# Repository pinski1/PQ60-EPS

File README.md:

#PQ60-EPS
An Electronic Power System in the PocketQube 60 form factor

**Untested**

The PQ60 Electrical Power System board is a system board for pico-satellites that connects to the solar arrays, charges the internal battery and provides protected battery voltage and protected +3V3 regulated supplies.

Uses @Pinski1's [PQ60-Template](https://github.com/pinski1/PQ60-Template) as the starting point for the design.

##Features
* Integrated active solar array maximum power point tracking.
* Battery charge management for Lithium Ion and Lithium Polymer batteries.
* Battery under-voltage protection.
* 3.3V and Raw Battery buses with over-current, over-voltage and reverse voltage protection.
* Monitoring of voltage, current and power of the solar cells, battery voltage and +3V3 via I<sup>2</sup>C interface.
* Kill switch connector to disable the satellite while in deployment tube.
* Compatible with the updated [PQ60 standard](http://pq60.info/).

##To Do
- [ ] Order PCBs
- [ ] Generate, format and order parts list
- [ ] Write firmware for KL05

##System

<!-- Block diagram -->

###Top
Telemetry of the EPS is provided on I<sup>2</sup>C by the Freescale [KL05](http://www.freescale.com/webapp/sps/site/prod_summary.jsp?code=KL0) ARM Cortex-M0 micro-controller which monitors the voltage, current and power at two points:

* The output of the raw battery 
* The output of the +3.3 Volt regulator

This will give real-time figures for the power flowing into the battery as well as the power being consumed by system loads. It also monitors the status pins and makes them available.

To protect this mission critical board against faults on other boards both the raw battery and regulated outputs have protection components to guard against over voltage, reverse voltage and over current. This is provided by Texas Instruments chip [TPS2553](http://www.ti.com/product/tps2553).

To ensure that the satellite logic is powered up successfully a Microchip [MCP130T](http://www.microchip.com/wwwproducts/Devices.aspx?product=MCP130) reset supervisor will hold the reset pin low until the the +3.3 Volt regulated supply is stable when it will release the reset pin.

###MPPT
To ensure that the maximum energy is harvested from the solar cells they are connected to a Maximum Power Point Tracker (MPPT). This reduces the current draw so as to efficiently transfer the harvested energy to the battery. This function is provided by a LinearTech [LTC3105](http://www.linear.com/product/LTC3105).

###IDIODE
To combine the 2 MPPT outputs a set of ideal diodes are used. These combine total energy harvested from the solar arrays and provide it to the Battery Management System (BMS). This function is provided by a LinearTech [LTC4413](http://www.linear.com/product/LTC4413).

###BMS
To store the energy from the solar arrays for future use it must be used to charge a battery. This stored energy can be used for the steady state operations of the satellite as well as peak operations such as transmitting or receiving data via the radio. This function is provided by a [MAX8606](http://www.maximintegrated.com/en/products/power/battery-management/MAX8606.html).

###SMPS
To provide a regulated +3.3 Volts a switched mode power supply is used. This converts the battery voltage to a stable +3.3 Volts and provides up to 750 milliamps of current to the rest of the subsystems. This function is provided by a [TPS63001](http://www.ti.com/product/tps63001).

##Connection Diagram

<!-- image -->

|Connector|     Type      |     Use        |
|---------|---------------|----------------|
|X2,3     | 4 way JST SHT | 2 Solar Arrays |
|X4       | 3 way JST SHT | Battery        |
|X5       | 2 way JST SHT | Kill Switch(s) |
|X1-Top   | 60 way FX6C   | PQ60 interface |
|X1-Bot   | 60 way FX6C   | PQ60 interface |

##Licensing
The hardware is released under [Creative Commons Attribution 3.0](https://creativecommons.org/licenses/by/3.0/).

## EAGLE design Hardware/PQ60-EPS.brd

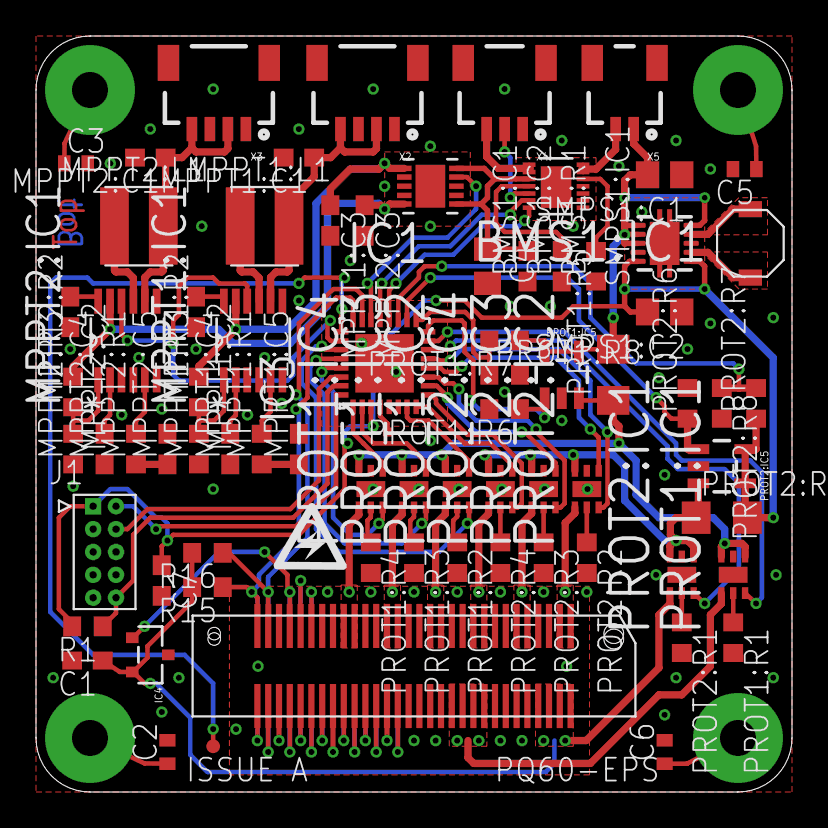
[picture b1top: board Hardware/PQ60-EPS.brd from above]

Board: 2 copper layers, 42.0 x 42.0 mm, 77 parts (1 on the bottom side), 95 nets.

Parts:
B1: PQ60-PINS; PQ60_PINS
BMS1:C1: 4.7uF; C0603
BMS1:C2: 100nF; C0603
BMS1:IC1: MAX8606; DFN300X300X80-15N
BMS1:R1: 2k; R0603
C1: 10nF; C0603
C2, C3, C5, C6: 100pF; C0402
C4: 4.7uF 10V; C0805
C7: 100nF; C0603
IC1: LTC4413; DFN300X300X80-11N
IC3: MKL05Z32VFM4; QFN50P500X500X100-33N
IC4: SOT23-R
J1: FTS-105-01-L-D; SAMTEC_FTS-105-01-L-D
MPPT1:C1, MPPT1:C3, MPPT2:C1, MPPT2:C3: 10uF; C0603
MPPT1:C2, MPPT2:C2: 1uF; C0603
MPPT1:C4, MPPT2:C4: 4.7uF; C0603
MPPT1:C5, MPPT2:C5: 10nF; C0603
MPPT1:IC1, MPPT2:IC1: LTC3105; SOP65P490X110-12N
MPPT1:L1, MPPT2:L1: 10uH; WE-TPC_3816
MPPT1:R1, MPPT2:R1: 75k; R0603
MPPT1:R2, MPPT2:R2: 1M33; R0603
MPPT1:R3, MPPT2:R3: 392k; R0603
PROT1:IC1, PROT1:IC2, PROT1:IC3, PROT1:IC4, PROT2:IC1, PROT2:IC2, PROT2:IC3, PROT2:IC4: TPS2553DRVT; SON65P200X200X80-7N
PROT1:IC5, PROT2:IC5: SOT23-5
PROT1:R1, PROT2:R1: 27k; R0603
PROT1:R2, PROT1:R3, PROT1:R4, PROT2:R2, PROT2:R3, PROT2:R4: 52k; R0603
PROT1:R5, PROT2:R5: 0R025; R1206
PROT1:R6, PROT2:R6: 10k 1%; R0603
PROT1:R7, PROT2:R7: 820k 1%; R0603
PROT1:R8, PROT2:R8: 200k 1%; R0603
R1: 10k; R0603
R15, R16: DNP; R0603
SMPS1:C1, SMPS1:C2: 10uF; C0805
SMPS1:IC1: TPS63001; DRC-S-PVSON-N10
SMPS1:L1: 2.2uH; VLF4012A
TP1: TEST-POINT2; PAD.02X.02
TP2: TEST-POINT3; PAD.03X.03
X1-BOT: FX8C-60S-SV
X1-TOP: FX8C-60P-SV
X2, X3: 1X04-1MM-RA
X4: 1X03-1MM-RA
X5: 1X02-1MM-RA

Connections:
!RST: IC4.1, X1-BOT.27, X1-TOP.27
+3V3_I_SEN: IC3.18, PROT2:IC5.1, PROT2:R6.1
+3V3_SW[0]_!FAULT!: IC3.14, PROT2:IC1.3
+3V3_SW[1]: PROT2:IC2.1, X1-BOT.1, X1-BOT.2, X1-TOP.1, X1-TOP.2
+3V3_SW[1]_!FAULT!: IC3.13, PROT2:IC2.3
+3V3_SW[1]_EN: IC3.12, PROT2:IC2.4
+3V3_SW[2]: PROT2:IC3.1, X1-BOT.5, X1-BOT.6, X1-TOP.5, X1-TOP.6
+3V3_SW[2]_!FAULT!: IC3.11, PROT2:IC3.3
+3V3_SW[2]_EN: IC3.10, PROT2:IC3.4
+3V3_SW[3]: PROT2:IC4.1, X1-BOT.9, X1-BOT.10, X1-TOP.9, X1-TOP.10
+3V3_SW[3]_!FAULT!: IC3.9, PROT2:IC4.3
+3V3_SW[3]_EN: IC3.8, PROT2:IC4.4
+3V3_UNPRO: C7.1, IC3.3, J1.1, PROT2:IC5.4, PROT2:IC5.5, PROT2:R5.2, PROT2:R7.1, R1.2, SMPS1:C2.2, SMPS1:IC1.1, SMPS1:IC1.10
+3V3_V_SEN: IC3.19, PROT2:R7.2, PROT2:R8.1
BMS1:BATT_PROG: BMS1:IC1.12, BMS1:R1.2
BMS1:VL: BMS1:C2.2, BMS1:IC1.4
BMS_!CHG!: BMS1:IC1.6, IC3.21
BMS_!PGD!: BMS1:IC1.7, IC3.20
GND: BMS1:C1.1, BMS1:C2.1, BMS1:IC1.8, BMS1:IC1.9, BMS1:IC1.10, BMS1:IC1.11, BMS1:IC1.15, BMS1:R1.1, C1.2, C2.2, C3.2, C4.2, C5.2, C6.2, C7.2, IC1.2, IC1.3, IC1.4, IC1.11, IC3.5, IC3.6, IC3.33, IC4.3, J1.3, J1.5, J1.7, J1.9, MPPT1:C1.2, MPPT1:C2.2, MPPT1:C3.2, MPPT1:C4.1, MPPT1:C5.2, MPPT1:IC1.3, MPPT1:IC1.6, MPPT1:IC1.7, MPPT1:R3.1, MPPT2:C1.2, MPPT2:C2.2, MPPT2:C3.2, MPPT2:C4.1, MPPT2:C5.2, MPPT2:IC1.3, MPPT2:IC1.6, MPPT2:IC1.7, MPPT2:R3.1, PROT1:IC1.5, PROT1:IC1.7, PROT1:IC2.5, PROT1:IC2.7, PROT1:IC3.5, PROT1:IC3.7, PROT1:IC4.5, PROT1:IC4.7, PROT1:IC5.2, PROT1:R1.2, PROT1:R2.2, PROT1:R3.2, PROT1:R4.2, PROT1:R6.2, PROT1:R8.2, PROT2:IC1.5, PROT2:IC1.7, PROT2:IC2.5, PROT2:IC2.7, PROT2:IC3.5, PROT2:IC3.7, PROT2:IC4.5, PROT2:IC4.7, PROT2:IC5.2, PROT2:R1.2, PROT2:R2.2, PROT2:R3.2, PROT2:R4.2, PROT2:R6.2, PROT2:R8.2, SMPS1:C1.1, SMPS1:C2.1, SMPS1:IC1.3, SMPS1:IC1.9, SMPS1:IC1.TH, SMPS1:IC1.TH@1, SMPS1:IC1.TH@2, X1-BOT.3, X1-BOT.4, X1-BOT.7, X1-BOT.8, X1-BOT.11, X1-BOT.12, X1-BOT.15, X1-BOT.16, X1-BOT.19, X1-BOT.20, X1-BOT.23, X1-BOT.24, X1-BOT.28, X1-BOT.45, X1-BOT.46, X1-BOT.47, X1-BOT.48, X1-BOT.53, X1-BOT.54, X1-BOT.55, X1-BOT.56, X1-TOP.3, X1-TOP.4, X1-TOP.7, X1-TOP.8, X1-TOP.11, X1-TOP.12, X1-TOP.15, X1-TOP.16, X1-TOP.19, X1-TOP.20, X1-TOP.23, X1-TOP.24, X1-TOP.28, X1-TOP.45, X1-TOP.46, X1-TOP.47, X1-TOP.48, X1-TOP.53, X1-TOP.54, X1-TOP.55, X1-TOP.56, X2.1, X2.3, X3.1, X3.3, X4.1
GPIO[0]: X1-BOT.25, X1-TOP.25
GPIO[1]: X1-BOT.26, X1-TOP.26
GPIO[2]: X1-BOT.34, X1-TOP.34
GPIO[3]: X1-BOT.35, X1-TOP.35
GPIO[4]: X1-BOT.36, X1-TOP.36
GPIO[5]: X1-BOT.37, X1-TOP.37
GPIO[6]: X1-BOT.38, X1-TOP.38
GPIO[7]: X1-BOT.39, X1-TOP.39
GPIO[8]: X1-BOT.40, X1-TOP.40
GPIO[9]: X1-BOT.41, X1-TOP.41
GPIO[10]: X1-BOT.42, X1-TOP.42
GPIO[11]: X1-BOT.43, X1-TOP.43
GPIO[12]: X1-BOT.44, X1-TOP.44
I2C_INT: IC3.25, TP2.P$1
I2C_SCL: IC3.23, R16.1, X1-BOT.29, X1-TOP.29
I2C_SDA: IC3.24, R15.1, X1-BOT.30, X1-TOP.30
IDIODE_STAT: IC1.9, IC3.22
MPPT1:AUX: MPPT1:C2.1, MPPT1:IC1.12
MPPT1:FB: MPPT1:IC1.1, MPPT1:R2.1, MPPT1:R3.2
MPPT1:LDO: MPPT1:C4.2, MPPT1:IC1.2
MPPT1:MPPC: MPPT1:IC1.5, MPPT1:R1.2
MPPT1:SW: MPPT1:IC1.9, MPPT1:L1.2
MPPT1:THM: MPPT1:C5.1, MPPT1:R1.1
MPPT2:AUX: MPPT2:C2.1, MPPT2:IC1.12
MPPT2:FB: MPPT2:IC1.1, MPPT2:R2.1, MPPT2:R3.2
MPPT2:LDO: MPPT2:C4.2, MPPT2:IC1.2
MPPT2:MPPC: MPPT2:IC1.5, MPPT2:R1.2
MPPT2:SW: MPPT2:IC1.9, MPPT2:L1.2
MPPT2:THM: MPPT2:C5.1, MPPT2:R1.1
MPPT_PGD: IC3.26, MPPT1:IC1.10, MPPT2:IC1.10
unnamed: B1.1, C2.1
unnamed: B1.2, C3.1
unnamed: B1.3, C5.1
unnamed: B1.4, C6.1
unnamed: IC3.4, TP1.P$1
PRO1: C1.1, IC4.2, PROT2:IC1.1, R15.2, R16.2, X1-BOT.57, X1-BOT.58, X1-BOT.59, X1-BOT.60, X1-TOP.57, X1-TOP.58, X1-TOP.59, X1-TOP.60
PROT1:IN_SEN: PROT1:IC1.4, PROT1:IC1.6, PROT1:IC2.6, PROT1:IC3.6, PROT1:IC4.6, PROT1:IC5.3, PROT1:R5.1
PROT1:I_LIM_SW1: PROT1:IC2.2, PROT1:R2.1
PROT1:I_LIM_SW2: PROT1:IC3.2, PROT1:R3.1
PROT1:I_LIM_SW3: PROT1:IC4.2, PROT1:R4.1
PROT1:I_LIM_VCC: PROT1:IC1.2, PROT1:R1.1
PROT2:IN_SEN: PROT2:IC1.4, PROT2:IC1.6, PROT2:IC2.6, PROT2:IC3.6, PROT2:IC4.6, PROT2:IC5.3, PROT2:R5.1
PROT2:I_LIM_SW1: PROT2:IC2.2, PROT2:R2.1
PROT2:I_LIM_SW2: PROT2:IC3.2, PROT2:R3.1
PROT2:I_LIM_SW3: PROT2:IC4.2, PROT2:R4.1
PROT2:I_LIM_VCC: PROT2:IC1.2, PROT2:R1.1
RESET: IC3.31, J1.10, R1.1
SMPS1:N$1: SMPS1:IC1.4, SMPS1:L1.P$1
SMPS1:N$2: SMPS1:IC1.2, SMPS1:L1.P$2
SOLAR[1..2]: MPPT1:C1.1, MPPT1:IC1.8, MPPT1:L1.1, X2.2, X2.4
SOLAR[3..4]: MPPT2:C1.1, MPPT2:IC1.8, MPPT2:L1.1, X3.2, X3.4
SPI_MISO: X1-BOT.32, X1-TOP.32
SPI_MOSI: X1-BOT.31, X1-TOP.31
SPI_SCK: X1-BOT.33, X1-TOP.33
SWD_CLK: IC3.30, J1.4
SWD_DIO: IC3.32, J1.2
S_ARRAY_1: IC1.1, MPPT1:C3.1, MPPT1:IC1.11, MPPT1:R2.2
S_ARRAY_2: IC1.5, MPPT2:C3.1, MPPT2:IC1.11, MPPT2:R2.2
THM: BMS1:IC1.5, X4.2
VBAT: PROT1:IC1.1, X1-BOT.49, X1-BOT.50, X1-BOT.51, X1-BOT.52, X1-TOP.49, X1-TOP.50, X1-TOP.51, X1-TOP.52
VBAT_I_SEN: IC3.16, PROT1:IC5.1, PROT1:R6.1
VBAT_SW[0]_!FAULT!: IC3.15, PROT1:IC1.3
VBAT_SW[1]: PROT1:IC2.1, X1-BOT.13, X1-BOT.14, X1-TOP.13, X1-TOP.14
VBAT_SW[1]_!FAULT!: IC3.27, PROT1:IC2.3
VBAT_SW[1]_EN: IC3.7, PROT1:IC2.4
VBAT_SW[2]: PROT1:IC3.1, X1-BOT.17, X1-BOT.18, X1-TOP.17, X1-TOP.18
VBAT_SW[2]_!FAULT!: IC3.28, PROT1:IC3.3
VBAT_SW[2]_EN: IC3.2, PROT1:IC3.4
VBAT_SW[3]: PROT1:IC4.1, X1-BOT.21, X1-BOT.22, X1-TOP.21, X1-TOP.22
VBAT_SW[3]_!FAULT!: IC3.29, PROT1:IC4.3
VBAT_SW[3]_EN: IC3.1, PROT1:IC4.4
VBAT_V_SEN: IC3.17, PROT1:R7.2, PROT1:R8.1
VSOL: BMS1:C1.2, BMS1:IC1.3, C4.1, IC1.6, IC1.10
VSYS: BMS1:IC1.13, BMS1:IC1.14, X5.2
VSYS_SW: PROT1:IC5.4, PROT1:IC5.5, PROT1:R5.2, PROT1:R7.1, SMPS1:C1.2, SMPS1:IC1.5, SMPS1:IC1.6, SMPS1:IC1.7, SMPS1:IC1.8, X5.1
V_BAT: BMS1:IC1.1, BMS1:IC1.2, X4.3

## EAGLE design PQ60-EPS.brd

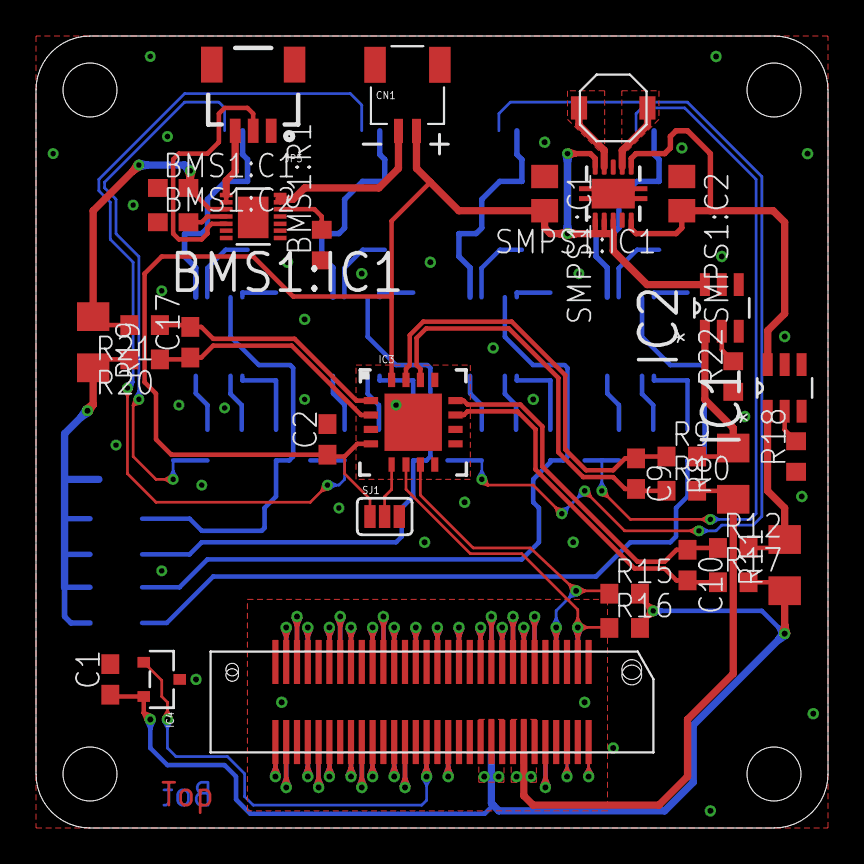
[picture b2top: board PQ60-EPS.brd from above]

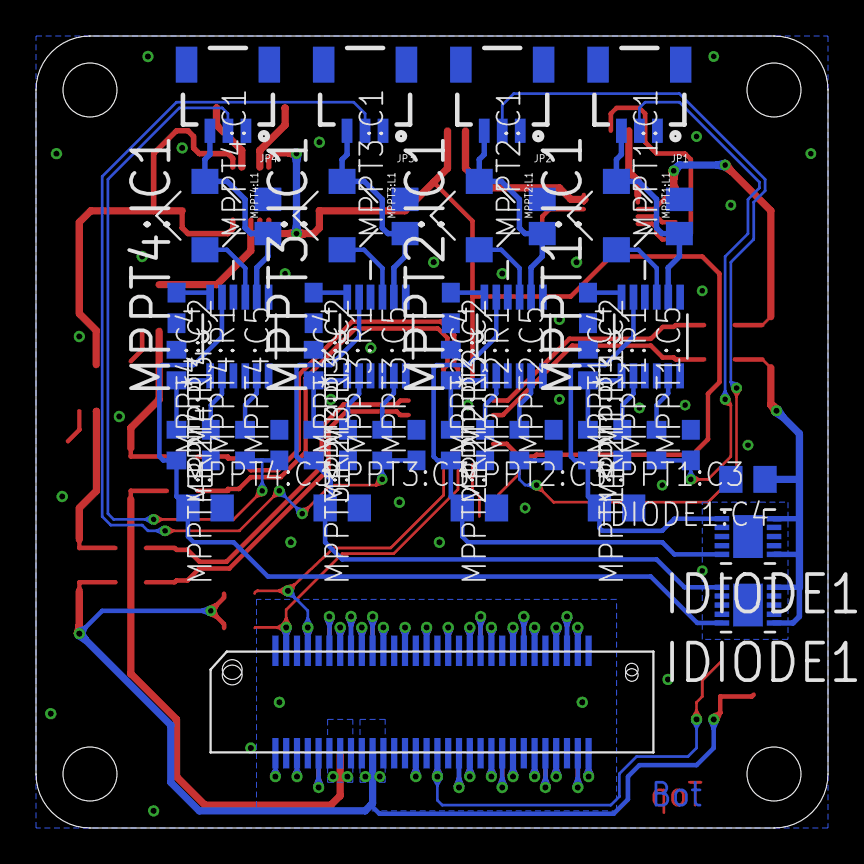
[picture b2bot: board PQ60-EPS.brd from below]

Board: 2 copper layers, 44.0 x 44.0 mm, 83 parts (48 on the bottom side), 92 nets.

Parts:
B1: PQ60-NOPINS; PQ60_NOPINS
BMS1:C1: 4.7uF; C0603
BMS1:C2: 100nF; C0603
BMS1:IC1: MAX8606; DFN300X300X80-15N
BMS1:R1: 2k; R0603
C1: 10nF; C0603
C2, C9, C10, C17: 100nF; C0603
CN1: JSTSH2
IC1, IC2: TPS2552; SOT95P280X145-6N
IC3: INA3221; QFN16
IC4: SOT23-R
IDIODE1:C4: 10uF; C0805
IDIODE1:IC1, IDIODE1:IC2: LTC4413; DFN300X300X80-11N
JP1, JP2, JP3, JP4, JP5: 1X03-1MM-RA
MPPT1:C1, MPPT1:C3, MPPT2:C1, MPPT2:C3, MPPT3:C1, MPPT3:C3, MPPT4:C1, MPPT4:C3: 10uF; C0805
MPPT1:C2, MPPT2:C2, MPPT3:C2, MPPT4:C2: 1uF; C0603
MPPT1:C4, MPPT2:C4, MPPT3:C4, MPPT4:C4: 4.7uF; C0603
MPPT1:C5, MPPT2:C5, MPPT3:C5, MPPT4:C5: 10nF; C0603
MPPT1:IC1, MPPT2:IC1, MPPT3:IC1, MPPT4:IC1: LTC3105; SOP65P490X110-12N
MPPT1:L1, MPPT2:L1, MPPT3:L1, MPPT4:L1: 10uH; CDRH3D28
MPPT1:R1, MPPT2:R1, MPPT3:R1, MPPT4:R1: 75k; R0603
MPPT1:R2, MPPT2:R2, MPPT3:R2, MPPT4:R2: 1M33; R0603
MPPT1:R3, MPPT2:R3, MPPT3:R3, MPPT4:R3: 392k; R0603
R8, R11, R19: 0R2; R1206
R9, R10, R12, R17, R20, R21: 10; R0603
R15, R16: DNP; R0603
R18, R22: 47k; R0603
SJ1: SJ_3_PASTE2&3
SMPS1:C1, SMPS1:C2: 10uF; C0805
SMPS1:IC1: TPS63001; DRC-S-PVSON-N10
SMPS1:L1: 2.2uH; VLF4012A
X1-BOT: FX8C-60S-SV
X1-TOP: FX8C-60P-SV

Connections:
!RST: IC4.1, X1-BOT.45, X1-TOP.45
+3V3: C1.1, IC4.2, R11.1, R15.2, R16.2, R17.2, X1-BOT.50, X1-BOT.51, X1-BOT.52, X1-TOP.50, X1-TOP.51, X1-TOP.52
+3V3_OUT: IC1.1, R11.2, R12.2
+3V3_SW[1]: X1-BOT.9, X1-TOP.9
+3V3_SW[2]: X1-BOT.10, X1-TOP.10
+3V3_SW[3]: X1-BOT.11, X1-TOP.11
+3V3_UNPRO: IC1.6, SMPS1:C2.2, SMPS1:IC1.1, SMPS1:IC1.10
A0: IC3.5, SJ1.2
BMS1:BATT_PROG: BMS1:IC1.12, BMS1:R1.2
BMS1:VL: BMS1:C2.2, BMS1:IC1.4
GND: BMS1:C1.1, BMS1:C2.1, BMS1:IC1.8, BMS1:IC1.9, BMS1:IC1.10, BMS1:IC1.11, BMS1:IC1.15, BMS1:R1.1, C1.2, C2.2, IC1.5, IC2.5, IC3.3, IC3.EXP, IC4.3, IDIODE1:C4.2, IDIODE1:IC1.2, IDIODE1:IC1.3, IDIODE1:IC1.4, IDIODE1:IC1.11, IDIODE1:IC2.2, IDIODE1:IC2.3, IDIODE1:IC2.4, IDIODE1:IC2.11, JP1.1, JP2.1, JP3.1, JP4.1, JP5.1, MPPT1:C1.2, MPPT1:C2.2, MPPT1:C3.2, MPPT1:C4.1, MPPT1:C5.2, MPPT1:IC1.3, MPPT1:IC1.6, MPPT1:IC1.7, MPPT1:R3.1, MPPT2:C1.2, MPPT2:C2.2, MPPT2:C3.2, MPPT2:C4.1, MPPT2:C5.2, MPPT2:IC1.3, MPPT2:IC1.6, MPPT2:IC1.7, MPPT2:R3.1, MPPT3:C1.2, MPPT3:C2.2, MPPT3:C3.2, MPPT3:C4.1, MPPT3:C5.2, MPPT3:IC1.3, MPPT3:IC1.6, MPPT3:IC1.7, MPPT3:R3.1, MPPT4:C1.2, MPPT4:C2.2, MPPT4:C3.2, MPPT4:C4.1, MPPT4:C5.2, MPPT4:IC1.3, MPPT4:IC1.6, MPPT4:IC1.7, MPPT4:R3.1, R18.1, R22.1, SJ1.3, SMPS1:C1.1, SMPS1:C2.1, SMPS1:IC1.3, SMPS1:IC1.9, SMPS1:IC1.TH, SMPS1:IC1.TH@1, SMPS1:IC1.TH@2, X1-BOT.1, X1-BOT.3, X1-BOT.5, X1-BOT.12, X1-BOT.14, X1-BOT.16, X1-BOT.18, X1-BOT.22, X1-BOT.26, X1-BOT.30, X1-BOT.33, X1-BOT.37, X1-BOT.41, X1-BOT.44, X1-BOT.46, X1-BOT.48, X1-BOT.49, X1-BOT.57, X1-BOT.59, X1-TOP.1, X1-TOP.3, X1-TOP.5, X1-TOP.12, X1-TOP.14, X1-TOP.16, X1-TOP.18, X1-TOP.22, X1-TOP.26, X1-TOP.30, X1-TOP.33, X1-TOP.37, X1-TOP.41, X1-TOP.44, X1-TOP.46, X1-TOP.48, X1-TOP.49, X1-TOP.57, X1-TOP.59
GPIO[1]: X1-BOT.19, X1-TOP.19
GPIO[2]: X1-BOT.20, X1-TOP.20
GPIO[3]: X1-BOT.21, X1-TOP.21
GPIO[4]: X1-BOT.23, X1-TOP.23
GPIO[5]: X1-BOT.24, X1-TOP.24
GPIO[6]: X1-BOT.25, X1-TOP.25
GPIO[7]: X1-BOT.27, X1-TOP.27
GPIO[8]: X1-BOT.28, X1-TOP.28
GPIO[9]: X1-BOT.29, X1-TOP.29
GPIO[10]: X1-BOT.31, X1-TOP.31
GPIO[11]: X1-BOT.32, X1-TOP.32
GPIO[12]: X1-BOT.38, X1-TOP.38
GPIO[13]: X1-BOT.39, X1-TOP.39
GPIO[14]: X1-BOT.40, X1-TOP.40
I2C_SCL: IC3.6, R16.1, X1-BOT.2, X1-TOP.2
I2C_SDA: IC3.7, R15.1, X1-BOT.4, X1-TOP.4
ILIMIT_3V3: IC1.2, R18.2
ILIMIT_VBUS: IC2.2, R22.2
IN1_N: C10.2, IC3.11, R17.1
IN1_P: C10.1, IC3.12, R12.1
IN2_N: C9.2, IC3.14, R10.1
IN2_P: C9.1, IC3.15, R9.1
IN3_N: C17.2, IC3.1, R21.1
IN3_P: C17.1, IC3.2, R20.1
MPPT1:AUX: MPPT1:C2.1, MPPT1:IC1.12
MPPT1:FB: MPPT1:IC1.1, MPPT1:R2.1, MPPT1:R3.2
MPPT1:LDO: MPPT1:C4.2, MPPT1:IC1.2
MPPT1:MPPC: MPPT1:IC1.5, MPPT1:R1.2
MPPT1:SW: MPPT1:IC1.9, MPPT1:L1.2
MPPT2:AUX: MPPT2:C2.1, MPPT2:IC1.12
MPPT2:FB: MPPT2:IC1.1, MPPT2:R2.1, MPPT2:R3.2
MPPT2:LDO: MPPT2:C4.2, MPPT2:IC1.2
MPPT2:MPPC: MPPT2:IC1.5, MPPT2:R1.2
MPPT2:SW: MPPT2:IC1.9, MPPT2:L1.2
MPPT3:AUX: MPPT3:C2.1, MPPT3:IC1.12
MPPT3:FB: MPPT3:IC1.1, MPPT3:R2.1, MPPT3:R3.2
MPPT3:LDO: MPPT3:C4.2, MPPT3:IC1.2
MPPT3:MPPC: MPPT3:IC1.5, MPPT3:R1.2
MPPT3:SW: MPPT3:IC1.9, MPPT3:L1.2
MPPT4:AUX: MPPT4:C2.1, MPPT4:IC1.12
MPPT4:FB: MPPT4:IC1.1, MPPT4:R2.1, MPPT4:R3.2
MPPT4:LDO: MPPT4:C4.2, MPPT4:IC1.2
MPPT4:MPPC: MPPT4:IC1.5, MPPT4:R1.2
MPPT4:SW: MPPT4:IC1.9, MPPT4:L1.2
NC@34: X1-BOT.34, X1-TOP.34
NC@35: X1-BOT.35, X1-TOP.35
NC@36: X1-BOT.36, X1-TOP.36
NC@42: X1-BOT.42, X1-TOP.42
NC@43: X1-BOT.43, X1-TOP.43
NC@56: X1-BOT.56, X1-TOP.56
SMPS1:N$1: SMPS1:IC1.4, SMPS1:L1.P$1
SMPS1:N$2: SMPS1:IC1.2, SMPS1:L1.P$2
SOLAR_1: JP1.3, MPPT1:C1.1, MPPT1:IC1.8, MPPT1:L1.1
SOLAR_2: JP2.3, MPPT2:C1.1, MPPT2:IC1.8, MPPT2:L1.1
SOLAR_3: JP3.3, MPPT3:C1.1, MPPT3:IC1.8, MPPT3:L1.1
SOLAR_4: JP4.3, MPPT4:C1.1, MPPT4:IC1.8, MPPT4:L1.1
SPI_CS: X1-BOT.47, X1-TOP.47
SPI_MISO: X1-BOT.15, X1-TOP.15
SPI_MOSI: X1-BOT.17, X1-TOP.17
SPI_SCK: X1-BOT.13, X1-TOP.13
S_ARRAY_1: IDIODE1:IC1.1, MPPT1:C3.1, MPPT1:IC1.11, MPPT1:R2.2
S_ARRAY_2: IDIODE1:IC1.5, MPPT2:C3.1, MPPT2:IC1.11, MPPT2:R2.2
S_ARRAY_3: IDIODE1:IC2.1, MPPT3:C3.1, MPPT3:IC1.11, MPPT3:R2.2
S_ARRAY_4: IDIODE1:IC2.5, MPPT4:C3.1, MPPT4:IC1.11, MPPT4:R2.2
TA1: JP1.2, MPPT1:C5.1, MPPT1:R1.1
TA2: JP2.2, MPPT2:C5.1, MPPT2:R1.1
TA3: JP3.2, MPPT3:C5.1, MPPT3:R1.1
TA4: JP4.2, MPPT4:C5.1, MPPT4:R1.1
THM: BMS1:IC1.5, JP5.2
USB_N: X1-BOT.58, X1-TOP.58
USB_P: X1-BOT.60, X1-TOP.60
VBAT: BMS1:IC1.1, BMS1:IC1.2, JP5.3
VBUS: R8.1, R10.2, X1-BOT.53, X1-BOT.54, X1-BOT.55, X1-TOP.53, X1-TOP.54, X1-TOP.55
VBUS_OUT: IC2.1, R8.2, R9.2
VBUS_SW[1]: X1-BOT.6, X1-TOP.6
VBUS_SW[2]: X1-BOT.7, X1-TOP.7
VBUS_SW[3]: X1-BOT.8, X1-TOP.8
VSOL: IDIODE1:C4.1, IDIODE1:IC1.6, IDIODE1:IC1.10, IDIODE1:IC2.6, IDIODE1:IC2.10, R19.2, R20.2
VSOL_SEN: BMS1:C1.2, BMS1:IC1.3, R19.1, R21.2
VSYS: BMS1:IC1.13, BMS1:IC1.14, CN1.1
VSYS_SW: C2.1, CN1.2, IC2.6, IC3.4, IC3.16, SJ1.1, SMPS1:C1.2, SMPS1:IC1.5, SMPS1:IC1.6, SMPS1:IC1.7, SMPS1:IC1.8

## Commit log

2015-03-01 Initial file check in.
2015-03-01 Filling out the README.markdown.
2015-03-01 minor updates to README.md
2015-03-01 Minor README.md update
2015-07-06 Updated to latest PQ60 standard and enhanced circuit,
2015-07-06 Update README.md
    Fixed image.

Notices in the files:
parts and their libraries:
SparkFun-Connectors: Licensing: Creative Commons ShareAlike 4.0 International - https://creativecommons.org/licenses/by-sa/4.0
SparkFun march 2012: Licensing: CC v3.0 Share-Alike You are welcome to use this library for commercial purposes.
